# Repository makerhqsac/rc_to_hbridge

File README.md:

# R/C to H-Bridge

A PCB to convert R/C PPM signals into H-Bridge compatible PWM and direction signals as used by many popular H bridge boards. This allows
the separation of the R/C signal processing from the H bridge, such that you can combine this board with small to very large H bridge
boards.

The default firmware for this board handles the mixing of the Throttle and Steering channels to drive two differential motors, aka "Tank Style". It also has two AUX inputs that map to two digital outputs that allow R/C channels to toggle the outputs LOW and HIGH based on the R/C value. This can be useful to add things like weapon arm/disarm, self-righting mechanisms, lights, etc.

Many H bridge boards in the 2A range are available on Amazon quite cheap, such as [This one](https://www.amazon.com/dp/B01CC8XI60) or
[This one](https://www.amazon.com/L9110S-Stepper-Driver-Atomic-Market/dp/B01ACIALJ4).

# The Board

# Powering

The board requires 5VDC power to operate. It can be powered either from the R/C inputs (which usually come from the R/C receiver which
  gets power from the ESC or BEC) or you can power directly to the + and - port next to the R/C inputs. If powering via the dedicated
  power port, you should disconnect the + in on the R/C inputs.

# Pins

## R/C

The R/C inputs connect directly to an R/C receiver. By default R/C center is 1500uS, and max throw is +/- 500uS in each direction.

All R/C inputs have a Dead Zone which when the input is +/- this value from center (1500uS) the value will not trigger any
change in outputs nor apply power changes to the motors. The default Dead Zone is 25uS.

* T :: Throttle input - expected to be neutral throttle at 1500uS R/C value
* S :: Steering input - expects neutral left/right travel at 1500uS R/C value
* A :: AUX A - Values above R/C center + Dead Zone will turn OUT A to HIGH, values below R/C center - Dead Zone will turn OUT A to LOW
* B :: AUX B - Same as AUX A, but controls OUT B

## H bridge

The H Bridge side of the board is designed to interface to H-Bridge with either 4 or 6 pin controllers. The EN pins contain
the PWM signal and the corresponding 1/2 or 3/4 pins will either be LOW/HIGH or HIGH/LOW based on the mixed input of the
throttle/steering R/C signals to control the direction of the motors. The actual PWM signal format will depend on if the
board is in 4 or 6 pin mode. This is detailed in the next section. The PWM signal is also affected by if breaking is enabled
or not.

To connect 6 pin H Bridges, simply connect the ENA/1/2 pins to the first motor inputs and ENB/3/4 to the second motors inputs.

To connect a 4 pin H Bridge, connect ENA/1 to the first motor and ENB/4 to the second. The 1 and 4 pins will toggle between
LOW and HIGH to control direction. If you need to change motor direction and cannot do so by reversing the motor wires, you
can use pins 2 and 3 instead.

## PWM Modes

This firmware supports 6 and 4 pin dual channel H-Bridge boards. The format for the PWM signal is different depending on
the PWM mode as well as if breaking is enabled. The mode can be adjusted by placing the board in configuration mode. To
enter configuration mode, make sure the R/C transmitter is on, place a jumper across the H-bridge pins 2 and 3 and then
power on the R/C to H-Bridge board. At power on, if the board sees H-bridge pins 2 and 3 connected together,
it will go into configuration mode.

Configuration mode can be seen by the R/C status LED blinking 5 times at startup. Then every 4 seconds, the R/C status
will blink a certain number of times, corresponding to the current active PWM mode. To change the mode, use the steering
channel all the way to the left or right to change the current mode. The following table outlines the different modes:

| Mode Number   | Mode Name                 | Common H-Bridge Chips |
| ------------- | ------------------------- | --------------------- |
| 1             | 4 PIN PWM, no breaking    | L9110S                |
| 2             | 4 PIN PWM, with breaking  | L9110S                |
| 3             | 6 PIN PWM, no breaking    | L-298                 |
| 4             | 6 PIN PWM, with breaking  | L-298                 |

After the desired configuration mode is set by using the steering channel, unplug the power to the R/C to H-Bridge board
and remove the jumper between H-Bridge pins 2 and 3. Powering the board will start it up in normal mode, outputting the
new mode to the PWM pins on the H-Bridge.

## Breaking

If breaking is enabled (PWM modes 2 or 4), then if the throttle is in the forward direction and you switch the throttle into
reverse, rather than instantly flipping the motors into reverse, a breaking operation is sent to the H-Bridge. It will remain
in the breaking state until the throttle returns back to center, and then the next time the throttle goes into reverse the
motors will actually be driven in reverse.

## OUT

The OUT ports A and B toggle from LOW to HIGH based on the R/C input signals connected to inputs A and B. There is also
5v power available on the OUT port.

## SERIAL

This port is designed as an expansion port for future use and/or hacking. It provides a TTL serial connection to the ATMega
chip along with 5v power.

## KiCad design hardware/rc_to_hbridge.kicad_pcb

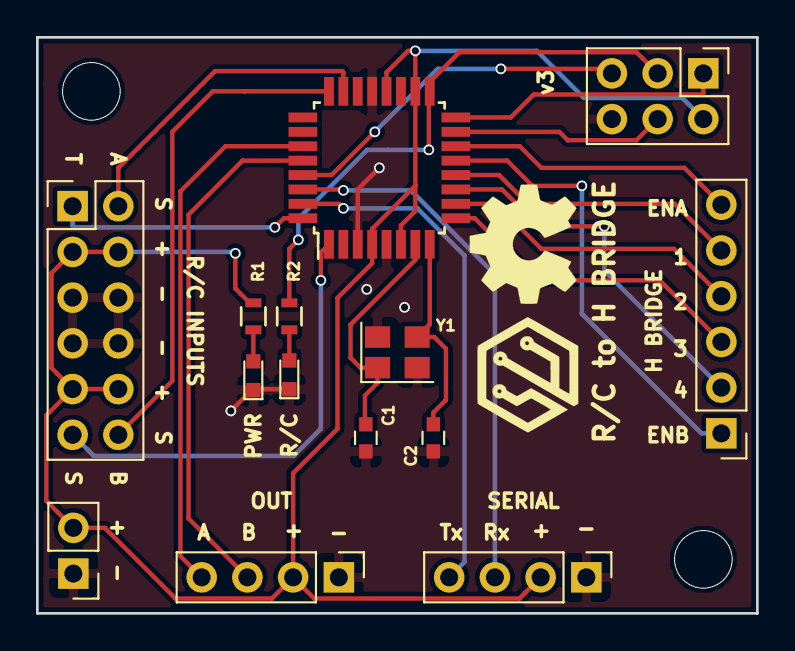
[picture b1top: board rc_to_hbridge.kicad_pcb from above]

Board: 2 copper layers, 40.0 x 32.0 mm, 14 parts (0 on the bottom side), 24 nets.

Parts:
C1, C2: 22pF; C_0603
CON1: AVR-ISP-6; Pin_Header_Straight_2x03_Pitch2.54mm
D1: RED; LED_0603
D2: GREEN; LED_0603
IC1: ATMEGA328-A; TQFP-32_7x7mm_Pitch0.8mm
P1, P5: CONN_01X04; Pin_Header_Straight_1x04_Pitch2.54mm
P2: CONN_01X02; Pin_Header_Straight_1x02_Pitch2.54mm
P3: CONN_02X06; Pin_Header_Straight_2x06_Pitch2.54mm
P4: CONN_01X06; Pin_Header_Straight_1x06_Pitch2.54mm
R1, R2: 330; R_0603
Y1: Crystal_GND24; Crystal_SMD_3225-4Pin_3.2x2.5mm

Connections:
/L_EN: IC1.14, P4.6
/L_FWD: IC1.12, P4.5
/L_REV: IC1.10, P4.4
/MISO: CON1.1, IC1.16
/MOSI: CON1.4, IC1.15
/OUT_A: IC1.27, P5.4
/OUT_B: IC1.28, P5.3
/RC_A: IC1.23, P3.2
/RC_B: IC1.24, P3.12
/RC_S: IC1.1, P3.11
/RC_T: IC1.32, P3.1
/RST: CON1.5, IC1.29
/RX: IC1.30, P1.3
/R_EN: IC1.13, P4.1
/R_FWD: IC1.11, P4.2
/R_REV: IC1.9, P4.3
/STATUS: CON1.3, IC1.17, R2.2
/TX: IC1.31, P1.4
GND: C1.1, C2.1, CON1.6, D1.1, D2.1, IC1.3, IC1.5, IC1.21, P1.1, P2.1, P3.5, P3.6, P3.7, P3.8, P5.1, Y1.2, Y1.4
unnamed: C1.2, IC1.7, Y1.1
unnamed: C2.2, IC1.8, Y1.3
unnamed: D1.2, R1.1
unnamed: D2.2, R2.1
VCC: CON1.2, IC1.4, IC1.6, IC1.18, IC1.20, P1.2, P2.2, P3.3, P3.4, P3.9, P3.10, P5.2, R1.2

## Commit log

2017-02-21 Initial import
2017-02-25 New PCB with aux out and serial. Updated firmware to match.
2017-02-27 fix footprints and better handle no rc
2017-03-09 Add docs
2017-03-09 Add schematic PDF
2017-04-04 Add break configuration ability
2017-04-04 break config fixes and tested working
2017-04-05 Clean up PWM mode names and document configuration feature
2017-04-09 Change how config mode is entered
2017-04-14 update image
2017-04-23 fix aux out pins
2017-05-06 Added system config image
2019-03-26 update hardware design for manufacturing - convert to kicad
